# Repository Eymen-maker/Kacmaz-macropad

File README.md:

HIII, this macropad is fully self/custom made. It has 6 keys and uses a Seeed XIAO RP2040 for software it uses QMK.

How to flash: just put .uf2 file in the microcontroller file (drag and drop).
In the current compiled code it says: 

key 1: 1

key 2: 2

key 3: 3

key 4: Hello, my name ıs Eymen. 

key 5: 5

key 6: 6

so it can write macros as well but be careful your keyboards language setting can break some words.

parts for the pcb are 6 through-hole 1N4148 Diodes, 6 MX-Style switches, 1 Seeed XIAO RP2040 and for the case you can use 4x M3x16mm screws, 4x M3x5mx4mm heatset inserts and the case would be 3d printed. (i didn't build the case for this example)

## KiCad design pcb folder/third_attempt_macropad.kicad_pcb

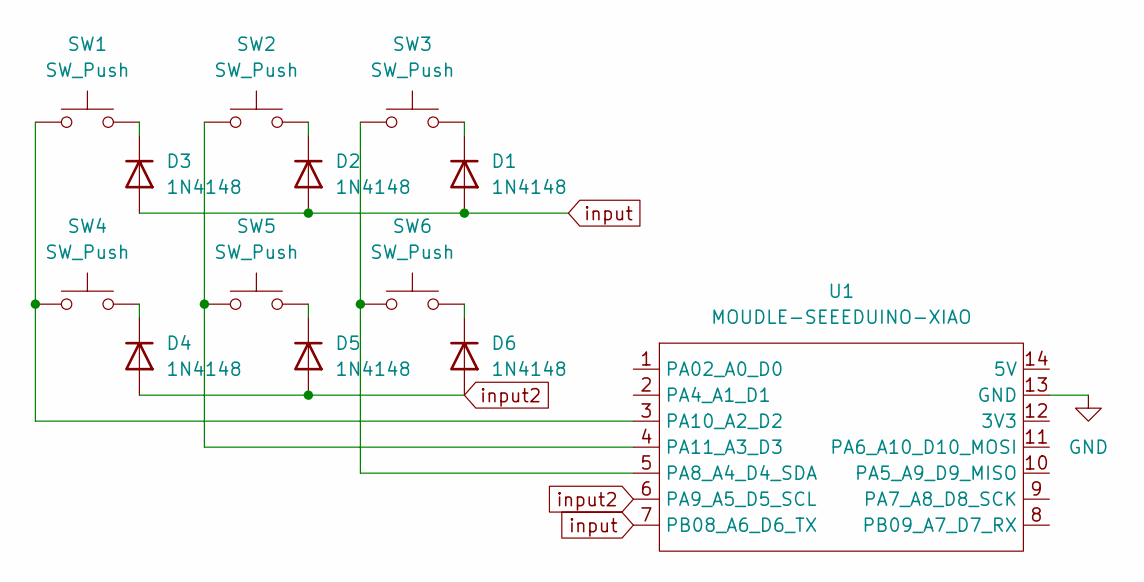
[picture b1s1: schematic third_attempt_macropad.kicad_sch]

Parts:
D1, D2, D3, D4, D5, D6: 1N4148; D_DO-35_SOD27_P7.62mm_Horizontal
SW1, SW2, SW3, SW4, SW5, SW6: SW_Push; SW_Cherry_MX_1.00u_PCB
U1: MOUDLE-SEEEDUINO-XIAO; XIAO-Generic-Hybrid-14P-2.54-21X17.8MM

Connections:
GND: U1.13 (GND)
unnamed: D1.1 (K), SW3.2
unnamed: D2.1 (K), SW2.2
unnamed: D3.1 (K), SW1.2
unnamed: D4.1 (K), SW4.2
unnamed: D5.1 (K), SW5.2
unnamed: D6.1 (K), SW6.2
unnamed: SW3.1, SW6.1, U1.5 (PA8_A4_D4_SDA)
unnamed: SW1.1, SW4.1, U1.3 (PA10_A2_D2)
unnamed: SW2.1, SW5.1, U1.4 (PA11_A3_D3)
el input: D1.2 (A), D2.2 (A), D3.2 (A), U1.7 (PB08_A6_D6_TX)
el input2: D4.2 (A), D5.2 (A), D6.2 (A), U1.6 (PA9_A5_D5_SCL)

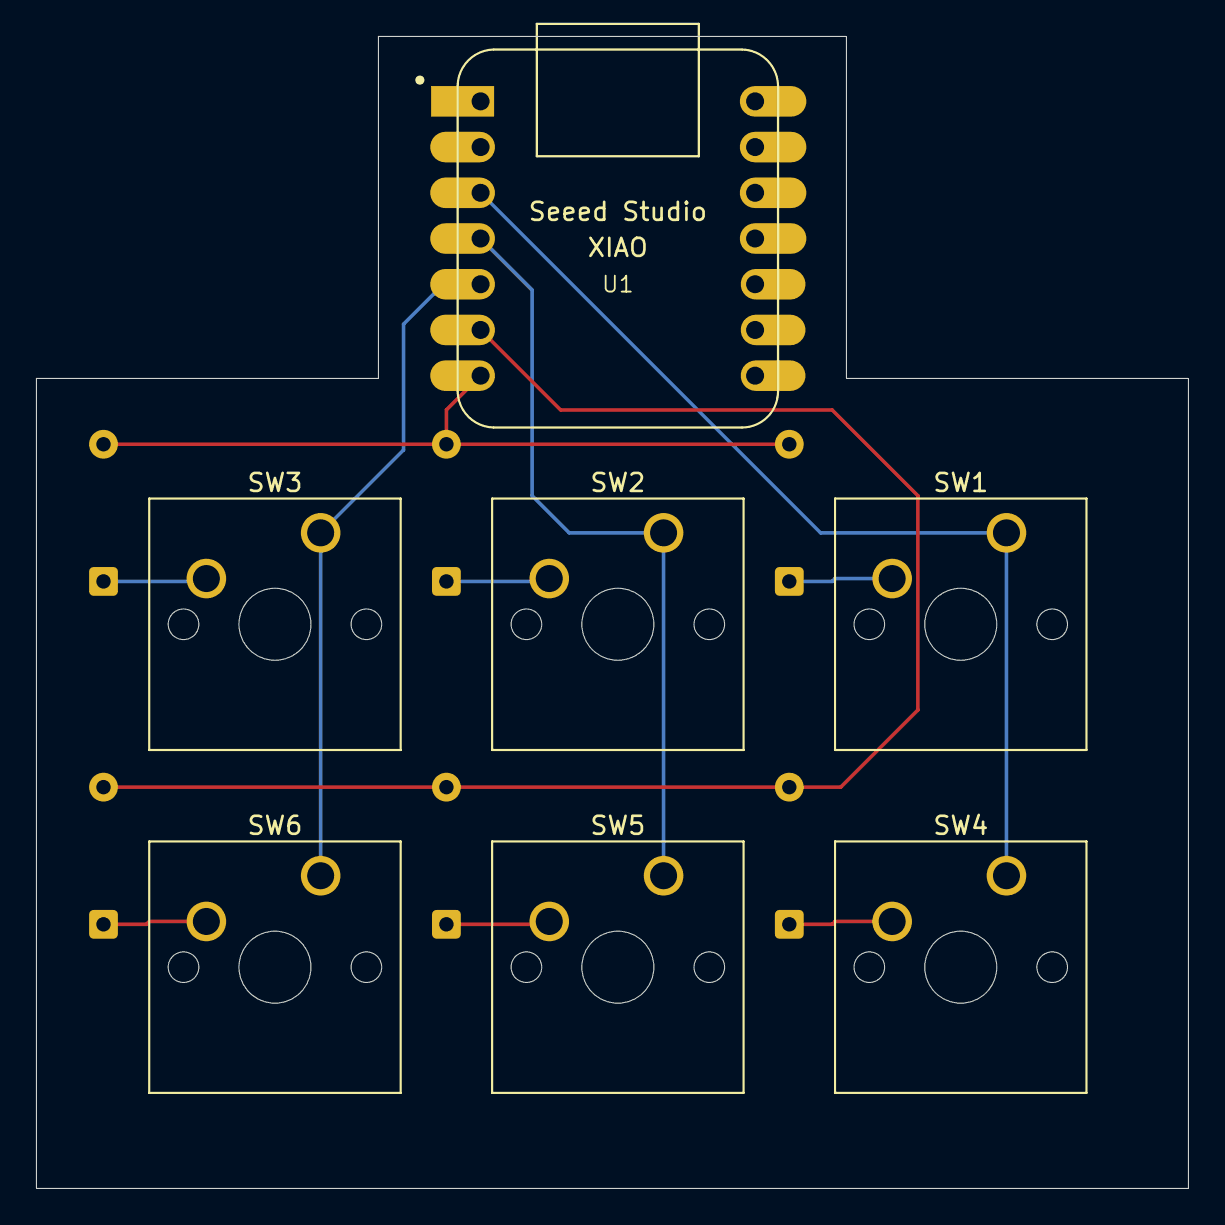
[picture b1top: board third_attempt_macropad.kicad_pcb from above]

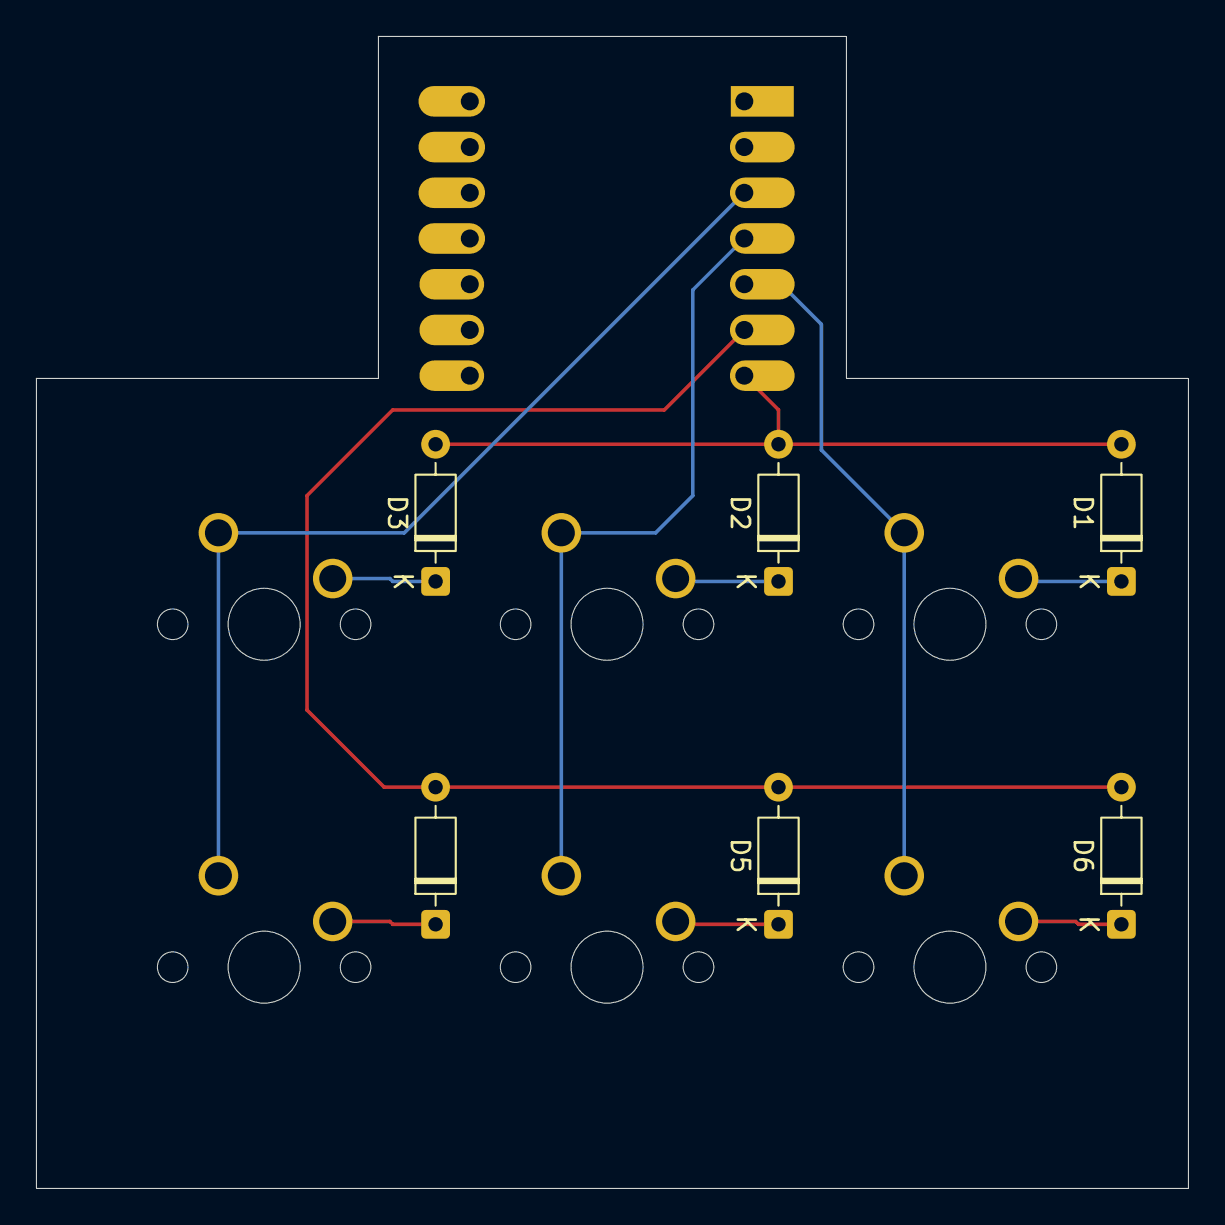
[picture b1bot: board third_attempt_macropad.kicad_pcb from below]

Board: 2 copper layers, 64.0 x 64.0 mm, 13 parts (6 on the bottom side), 11 nets.
